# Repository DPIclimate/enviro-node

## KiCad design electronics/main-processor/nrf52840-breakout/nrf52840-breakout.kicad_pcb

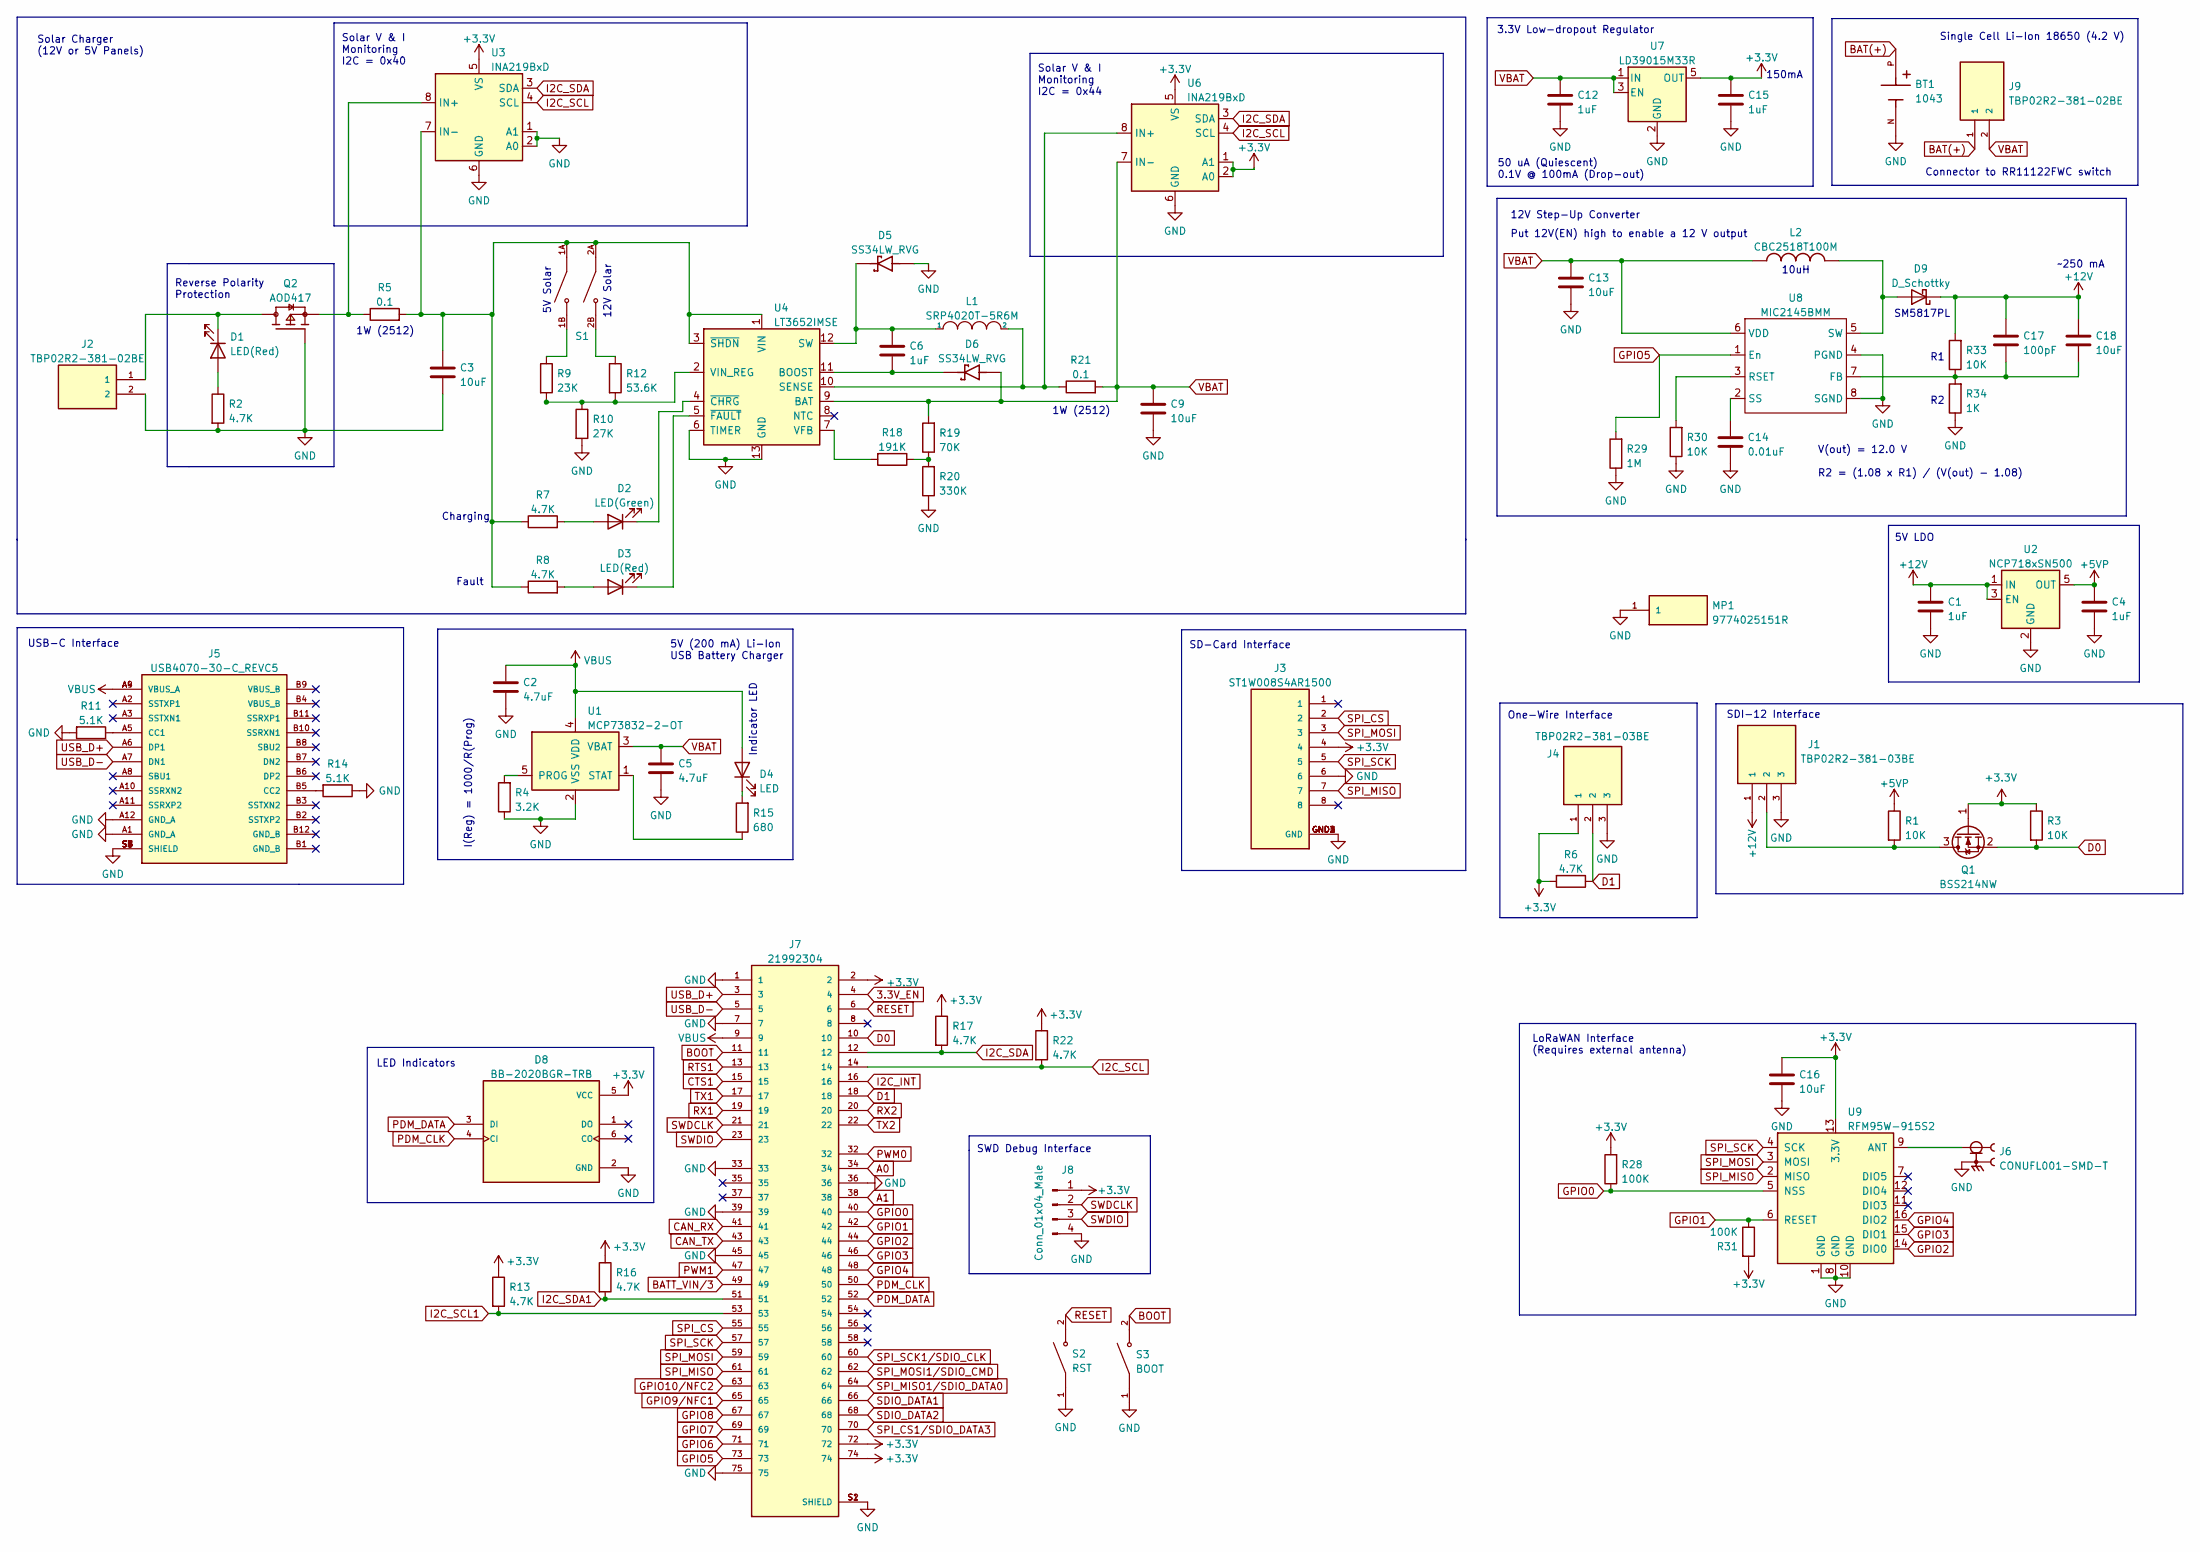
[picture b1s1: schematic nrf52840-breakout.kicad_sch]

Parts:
BT1: 1043; BAT_1043; PARTREV H
C1, C4, C6, C12, C15: 1uF; C_0805_2012Metric
C2, C5: 4.7uF; C_0805_2012Metric
C3, C9, C13, C16, C18: 10uF; C_0805_2012Metric
C14: 0.01uF; C_0805_2012Metric
C17: 100pF; C_0805_2012Metric
D1, D3: LED(Red); LED_0805_2012Metric
D2: LED(Green); LED_0805_2012Metric
D4: LED; LED_0805_2012Metric
D5, D6: SS34LW_RVG; SODFL3718X102N; PARTREV C2103
D8: BB-2020BGR-TRB; LED_BB-2020BGR-TRB; PARTREV --
D9: D_Schottky; SODFL3718X108N
J1, J4: TBP02R2-381-03BE; CUI_TBP02R2-381-03BE
J2, J9: TBP02R2-381-02BE; CUI_TBP02R2-381-02BE
J3: ST1W008S4AR1500; JAE_ST1W008S4AR1500; PARTREV 2
J5: USB4070-30-C_REVC5; GCT_USB4070-30-C_REVC5; PARTREV C5
J6: CONUFL001-SMD-T; LINX_CONUFL001-SMD-T; PARTREV B
J7: 21992304; TE_21992304
J8: Conn_01x04_Male; PinHeader_1x04_P2.54mm_Vertical
L1: SRP4020T-5R6M; IND_SRP4020TA-5R6M
L2: CBC2518T100M; INDC2518X200N
MP1: 9774025151R; WE_9774025151R; PARTREV 001.001
Q1: BSS214NW; SOT-323_SC-70
Q2: AOD417; DPAK228P994X240_3N; PARTREV U
R1, R3, R30, R33: 10K; R_0805_2012Metric
R2, R6, R7, R8, R13, R16, R17, R22: 4.7K; R_0805_2012Metric
R4: 3.2K; R_0805_2012Metric
R5, R21: 0.1; R_2512_6332Metric
R9: 23K; R_0805_2012Metric
R10: 27K; R_0805_2012Metric
R11, R14: 5.1K; R_0805_2012Metric
R12: 53.6K; R_0805_2012Metric
R15: 680; R_0805_2012Metric
R18: 191K; R_0805_2012Metric
R19: 70K; R_0805_2012Metric
R20: 330K; R_0805_2012Metric
R28, R31: 100K; R_0805_2012Metric
R29: 1M; R_0805_2012Metric
R34: 1K; R_0805_2012Metric
S1: DS04-254-2-02BK-SMT; SW_DS04-254-2-02BK-SMT; PARTREV V0.0
S2: RST; SW_PTS636_SM43J_SMTR_LFS; PARTREV 27 mar 19
S3: BOOT; SW_PTS636_SM43J_SMTR_LFS; PARTREV 27 mar 19
U1: MCP73832-2-OT; SOT-23-5
U2: NCP718xSN500; SOT-23-5
U3, U6: INA219BxD; SOIC-8_3.9x4.9mm_P1.27mm
U4: LT3652IMSE; MSOP-12-1EP_3x4mm_P0.65mm_EP1.65x2.85mm
U7: LD39015M33R; SOT-23-5
U8: MIC2145BMM
U9: RFM95W-915S2; XCVR_RFM95W-915S2

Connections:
3.3V_EN: J7.4
+3.3V: C15.1, C16.1, D8.5 (VCC), J3.4, J4.1, J7.2, J7.72, J7.74, J8.1, Q1.1 (G), R3.1, R6.2, R13.1, R16.1, R17.1, R22.1, R28.2, R31.2, U3.5 (VS), U6.1 (A1), U6.2 (A0), U6.5 (VS), U7.5 (OUT), U9.13 (3.3V)
+5VP: C4.1, R1.1, U2.5 (OUT)
+12V: C1.1, C17.1, C18.1, D9.1 (K), J1.1, R33.2, U2.1 (IN), U2.3 (EN)
A0: J7.34
A1: J7.38
BAT(+): BT1.P, J9.1
BATT_VIN/3: J7.49
BOOT: J7.11, S3.2
CAN_RX: J7.41
CAN_TX: J7.43
CTS1: J7.15
D0: J7.10, Q1.2 (S), R3.2
D1: J4.2, J7.18, R6.1
GND: BT1.N, C1.2, C2.2, C3.2, C4.2, C5.2, C9.2, C12.2, C13.2, C14.2, C15.2, C16.2, D5.A, D8.2 (GND), J1.3, J2.2, J3.6, J3.GND1 (GND), J3.GND2 (GND), J3.GND3 (GND), J3.GND4 (GND), J4.3, J5.A1 (GND_A), J5.A12 (GND_A), J5.S1 (SHIELD), J5.S2 (SHIELD), J5.S3 (SHIELD), J5.S4 (SHIELD), J5.S5 (SHIELD), J5.S6 (SHIELD), J5.S7 (SHIELD), J5.S8 (SHIELD), J6.2, J6.3, J7.1, J7.7, J7.33, J7.36, J7.39, J7.45, J7.75, J7.S1 (SHIELD), J7.S2 (SHIELD), J8.4, MP1.1, Q2.1, R2.2, R4.1, R10.2, R11.2, R14.1, R20.1, R29.1, R30.1, R34.1, S2.1, S3.1, U1.2 (VSS), U2.2 (GND), U3.1 (A1), U3.2 (A0), U3.6 (GND), U4.6 (TIMER), U4.13 (GND), U6.6 (GND), U7.2 (GND), U8.4 (PGND), U8.8 (SGND), U9.1 (GND), U9.8 (GND), U9.10 (GND)
GPIO0: J7.40, R28.1, U9.5 (NSS)
GPIO1: J7.42, R31.1, U9.6 (RESET)
GPIO2: J7.44, U9.14 (DIO0)
GPIO3: J7.46, U9.15 (DIO1)
GPIO4: J7.48, U9.16 (DIO2)
GPIO5: J7.73, R29.2, U8.1 (En)
GPIO6: J7.71
GPIO7: J7.69
GPIO8: J7.67
GPIO9/NFC1: J7.65
GPIO10/NFC2: J7.63
I2C_INT: J7.16
I2C_SCL: J7.14, R22.2, U3.4 (SCL), U6.4 (SCL)
I2C_SCL1: J7.53, R13.2
I2C_SDA: J7.12, R17.2, U3.3 (SDA), U6.3 (SDA)
I2C_SDA1: J7.51, R16.2
unnamed: C3.1, R5.2, R7.1, R8.1, S1.1A, S1.2A, U3.7 (IN-), U4.1 (VIN), U4.3 (~SHDN)
unnamed: C6.1, D5.C, L1.1, U4.12 (SW)
unnamed: C6.2, D6.C, U4.11 (BOOST)
unnamed: C14.1, U8.2 (SS)
unnamed: C17.2, C18.2, R33.1, R34.2, U8.7 (FB)
unnamed: D1.1 (K), J2.1, Q2.4
unnamed: D1.2 (A), R2.1
unnamed: D2.1 (K), U4.4 (~CHRG)
unnamed: D2.2 (A), R7.2
unnamed: D3.1 (K), U4.5 (~FAULT)
unnamed: D3.2 (A), R8.2
unnamed: D4.1 (K), R15.2
unnamed: D9.2 (A), L2.2, U8.5 (SW)
unnamed: J1.2, Q1.3 (D), R1.2
unnamed: J5.A5 (CC1), R11.1
unnamed: J5.B5 (CC2), R14.2
unnamed: J6.1, U9.9 (ANT)
unnamed: L1.2, R21.1, U4.10 (SENSE), U6.8 (IN+)
unnamed: Q2.3, R5.1, U3.8 (IN+)
unnamed: R4.2, U1.5 (PROG)
unnamed: R9.1, S1.1B
unnamed: R9.2, R10.1, R12.2, U4.2 (VIN_REG)
unnamed: R12.1, S1.2B
unnamed: R15.1, U1.1 (STAT)
unnamed: R18.1, R19.1, R20.2
unnamed: R18.2, U4.7 (VFB)
unnamed: R30.2, U8.3 (RSET)
PDM_CLK: D8.4 (CI), J7.50
PDM_DATA: D8.3 (DI), J7.52
PWM0: J7.32
PWM1: J7.47
RESET: J7.6, S2.2
RTS1: J7.13
RX1: J7.19
RX2: J7.20
SDIO_DATA1: J7.66
SDIO_DATA2: J7.68
SPI_CS: J3.2, J7.55
SPI_CS1/SDIO_DATA3: J7.70
SPI_MISO: J3.7, J7.61, U9.2 (MISO)
SPI_MISO1/SDIO_DATA0: J7.64
SPI_MOSI: J3.3, J7.59, U9.3 (MOSI)
SPI_MOSI1/SDIO_CMD: J7.62
SPI_SCK: J3.5, J7.57, U9.4 (SCK)
SPI_SCK1/SDIO_CLK: J7.60
SWDCLK: J7.21, J8.2
SWDIO: J7.23, J8.3
TX1: J7.17
TX2: J7.22
USB_D+: J5.A6 (DP1), J7.3
USB_D-: J5.A7 (DN1), J7.5
VBAT: C5.1, C9.1, C12.1, C13.1, D6.A, J9.2, L2.1, R19.2, R21.2, U1.3 (VBAT), U4.9 (BAT), U6.7 (IN-), U7.1 (IN), U7.3 (EN), U8.6 (VDD)
VBUS: C2.1, D4.2 (A), J5.A4 (VBUS_A), J5.A9 (VBUS_A), J7.9, U1.4 (VDD)

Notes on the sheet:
12V Step-Up Converter
SWD Debug Interface
Fault
1W (2512)
Put 12V(EN) high to enable a 12 V output
12V Solar
50 uA (Quiescent) 0.1V @ 100mA (Drop-out)
Solar Charger (12V or 5V Panels)
~250 mA
Indicator LED
SM5817PL
Solar V & I Monitoring I2C = 0x44
Solar V & I Monitoring I2C = 0x40
Connector to RR11122FWC switch
V(out) = 12.0 V R2 = (1.08 x R1) / (V(out) - 1.08)
5V Solar
5V LDO
5V (200 mA) Li-Ion USB Battery Charger
SD-Card Interface
I(Reg) = 1000/R(Prog)
SDI-12 Interface
150mA
Charging
10uH
USB-C Interface
LoRaWAN Interface (Requires external antenna)
Reverse Polarity Protection
Single Cell Li-Ion 18650 (4.2 V)
One-Wire Interface
3.3V Low-dropout Regulator
LED Indicators

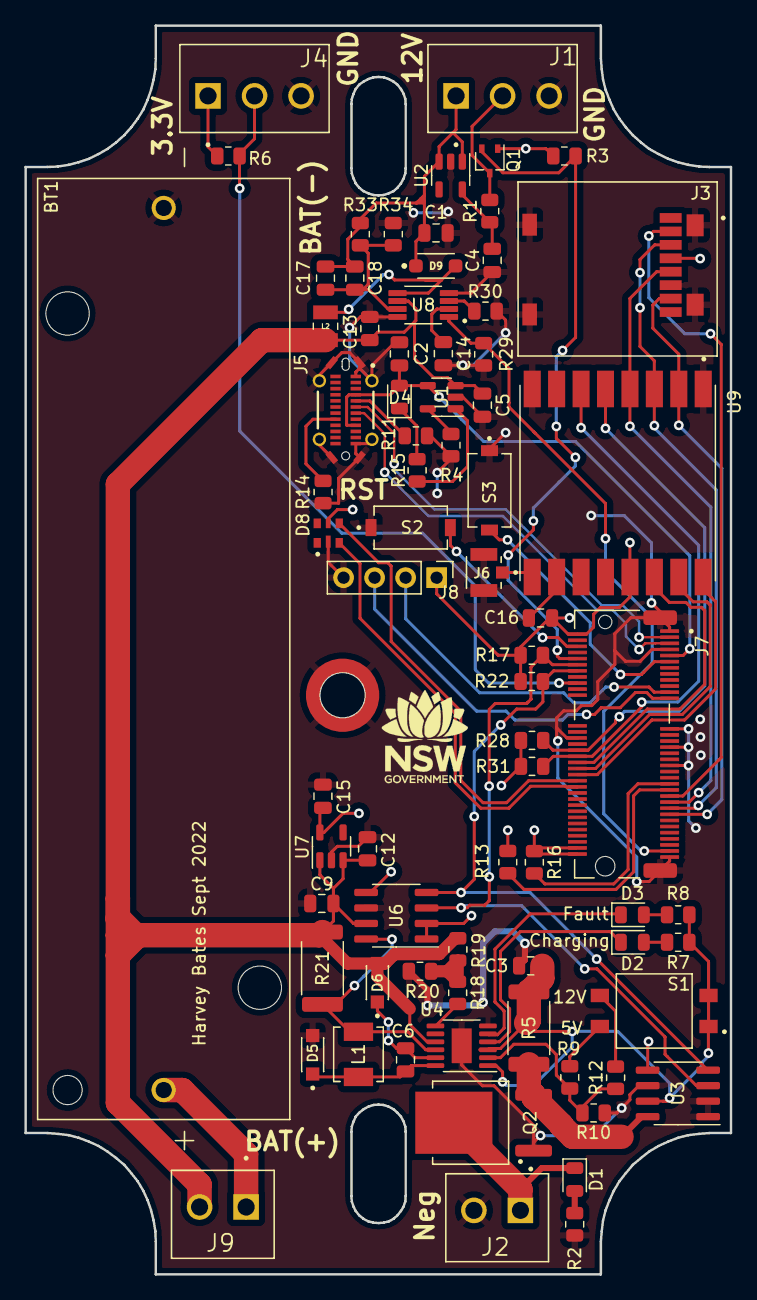
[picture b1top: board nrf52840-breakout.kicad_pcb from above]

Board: 2 copper layers, 57.7 x 102.2 mm, 76 parts (0 on the bottom side), 58 nets.
